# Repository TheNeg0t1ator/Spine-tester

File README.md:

# Spine-tester
A unit to test spine of arrows

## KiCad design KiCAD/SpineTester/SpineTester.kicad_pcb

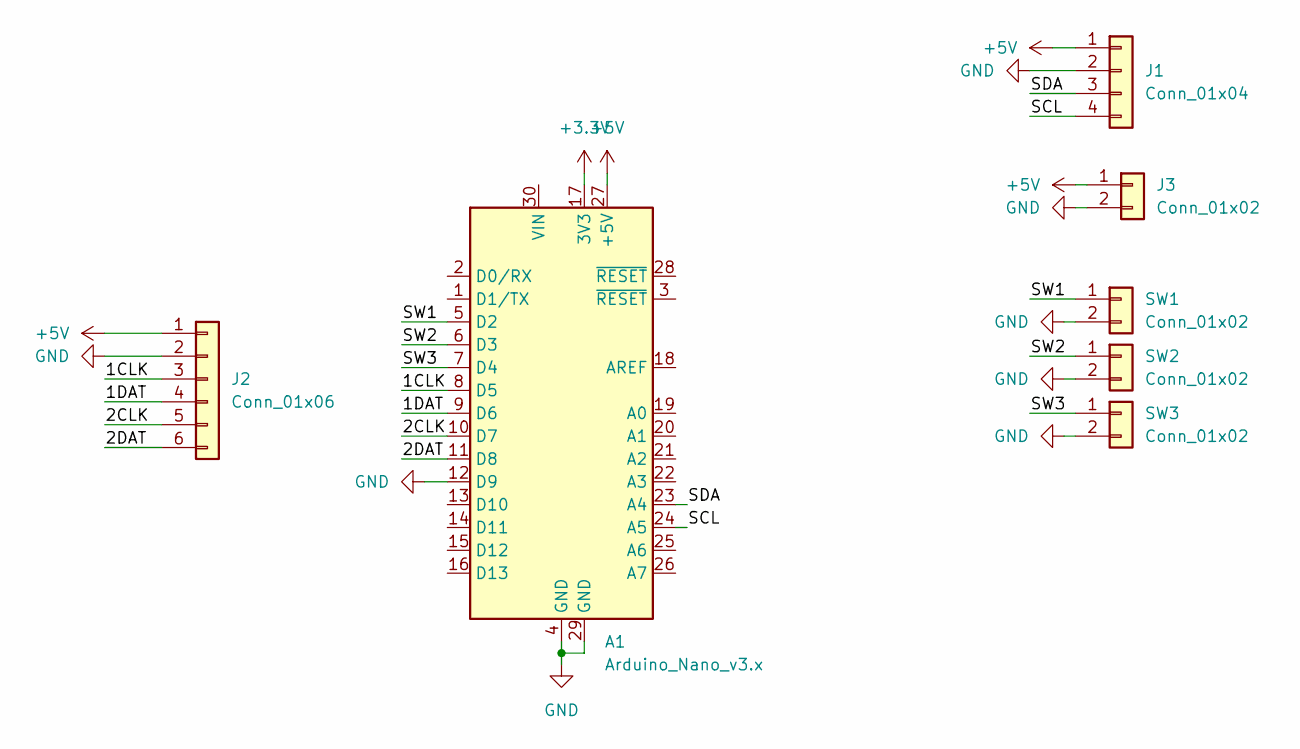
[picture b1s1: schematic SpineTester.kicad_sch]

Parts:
A1: Arduino_Nano_v3.x; Arduino_Nano
J1: Conn_01x04; PinHeader_1x04_P2.54mm_Vertical
J2: Conn_01x06; PinHeader_1x06_P2.54mm_Vertical
J3: Conn_01x02; PinHeader_1x02_P2.54mm_Vertical
SW1, SW2, SW3: Conn_01x02; PinHeader_1x02_P2.54mm_Vertical

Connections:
+3.3V: A1.17 (3V3)
+5V: A1.27 (+5V), J1.1, J2.1, J3.1
/1CLK: A1.8 (D5), J2.3
/1DAT: A1.9 (D6), J2.4
/2CLK: A1.10 (D7), J2.5
/2DAT: A1.11 (D8), J2.6
/SCL: A1.24 (A5), J1.4
/SDA: A1.23 (A4), J1.3
/SW1: A1.5 (D2), SW1.1
/SW2: A1.6 (D3), SW2.1
/SW3: A1.7 (D4), SW3.1
GND: A1.4 (GND), A1.12 (D9), A1.29 (GND), J1.2, J2.2, J3.2, SW1.2, SW2.2, SW3.2

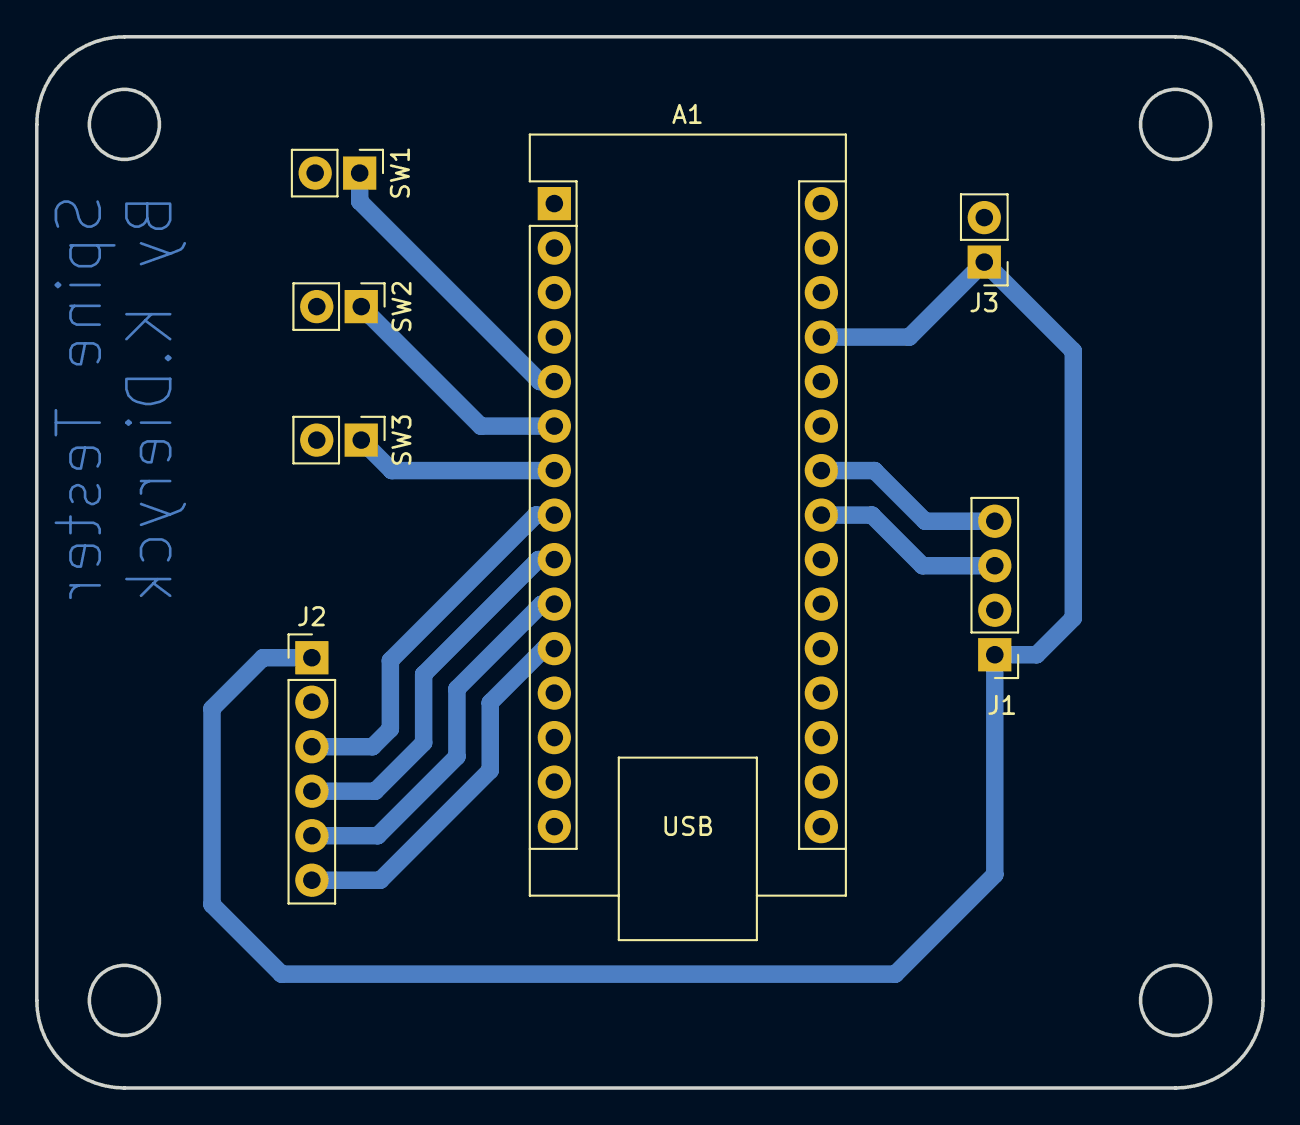
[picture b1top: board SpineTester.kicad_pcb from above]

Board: 2 copper layers, 70.0 x 60.0 mm, 7 parts (0 on the bottom side), 11 nets.

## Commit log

2024-06-22 addded pcb V1
2024-06-23 refactor
2024-06-27 modified startup message
